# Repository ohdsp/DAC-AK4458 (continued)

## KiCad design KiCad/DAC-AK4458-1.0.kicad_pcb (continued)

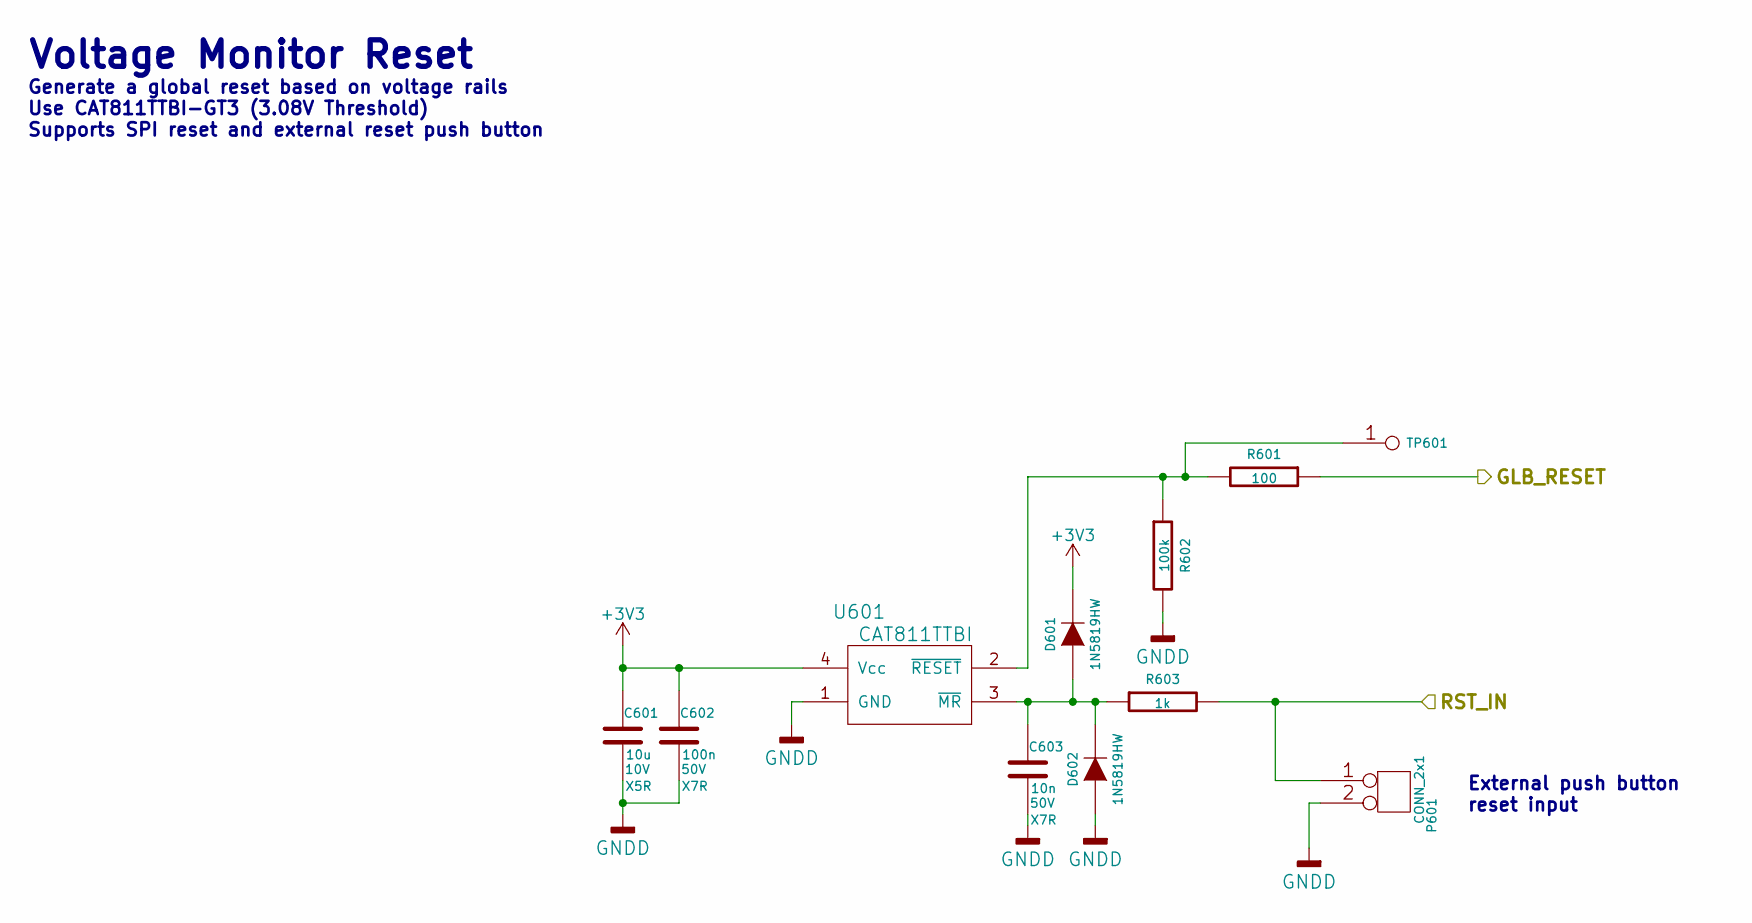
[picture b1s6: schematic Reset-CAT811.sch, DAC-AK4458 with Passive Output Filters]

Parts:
C601: 10u; SMD-0805; Voltage 10V; Tolerance 20%
C602: 100n; SMD-0805; Voltage 50V; Tolerance 10%
C603: 10n; SMD-0805; Voltage 50V; Tolerance 10%
D601, D602: 1N5819HW; DIODE-SOD-123
P601: CONN_2x1; CONN_SIL_2_1MM
R601: 100; SMD-0805; Tolerance 1%
R602: 100k; SMD-0805; Tolerance 1%
R603: 1k; SMD-0805; Tolerance 1%
TP601: PIN; TP-2mm
U601: CAT811TTBI; IC-SOT143

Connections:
+3V3: C601.1, C602.1, D601.2 (K), U601.4 (Vcc); also elsewhere on the board
/GLB_RST: R601.1; also elsewhere on the board
/Reset-CAT811/RST_IN: P601.1, R603.2; also elsewhere on the board
GNDA: C601.2, C602.2, C603.2, D602.1 (A), P601.2, R602.2, U601.1 (GND); also elsewhere on the board
unnamed: C603.1, D601.1 (A), D602.2 (K), R603.1, U601.3 (~MR)
unnamed: R601.2, R602.1, TP601.1, U601.2 (~RESET)

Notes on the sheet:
Generate a global reset based on voltage rails Use CAT811TTBI−GT3 (3.08V Threshold) Supports SPI reset and external reset push button
Voltage Monitor Reset
External push button reset input

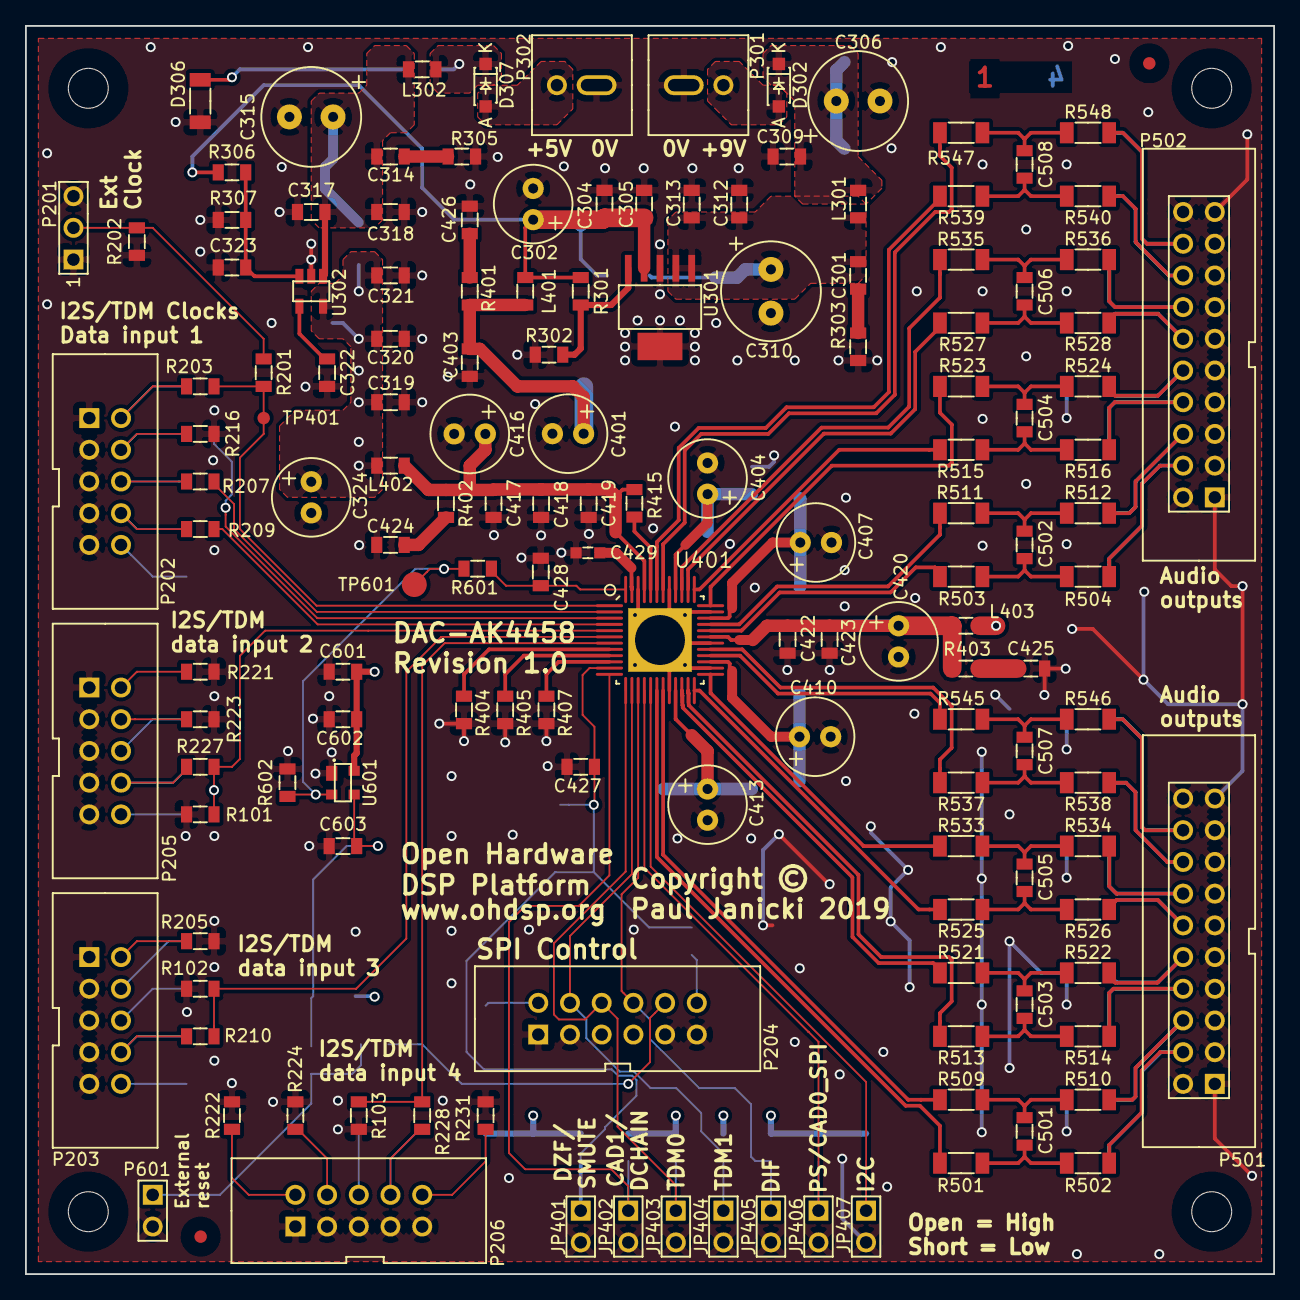
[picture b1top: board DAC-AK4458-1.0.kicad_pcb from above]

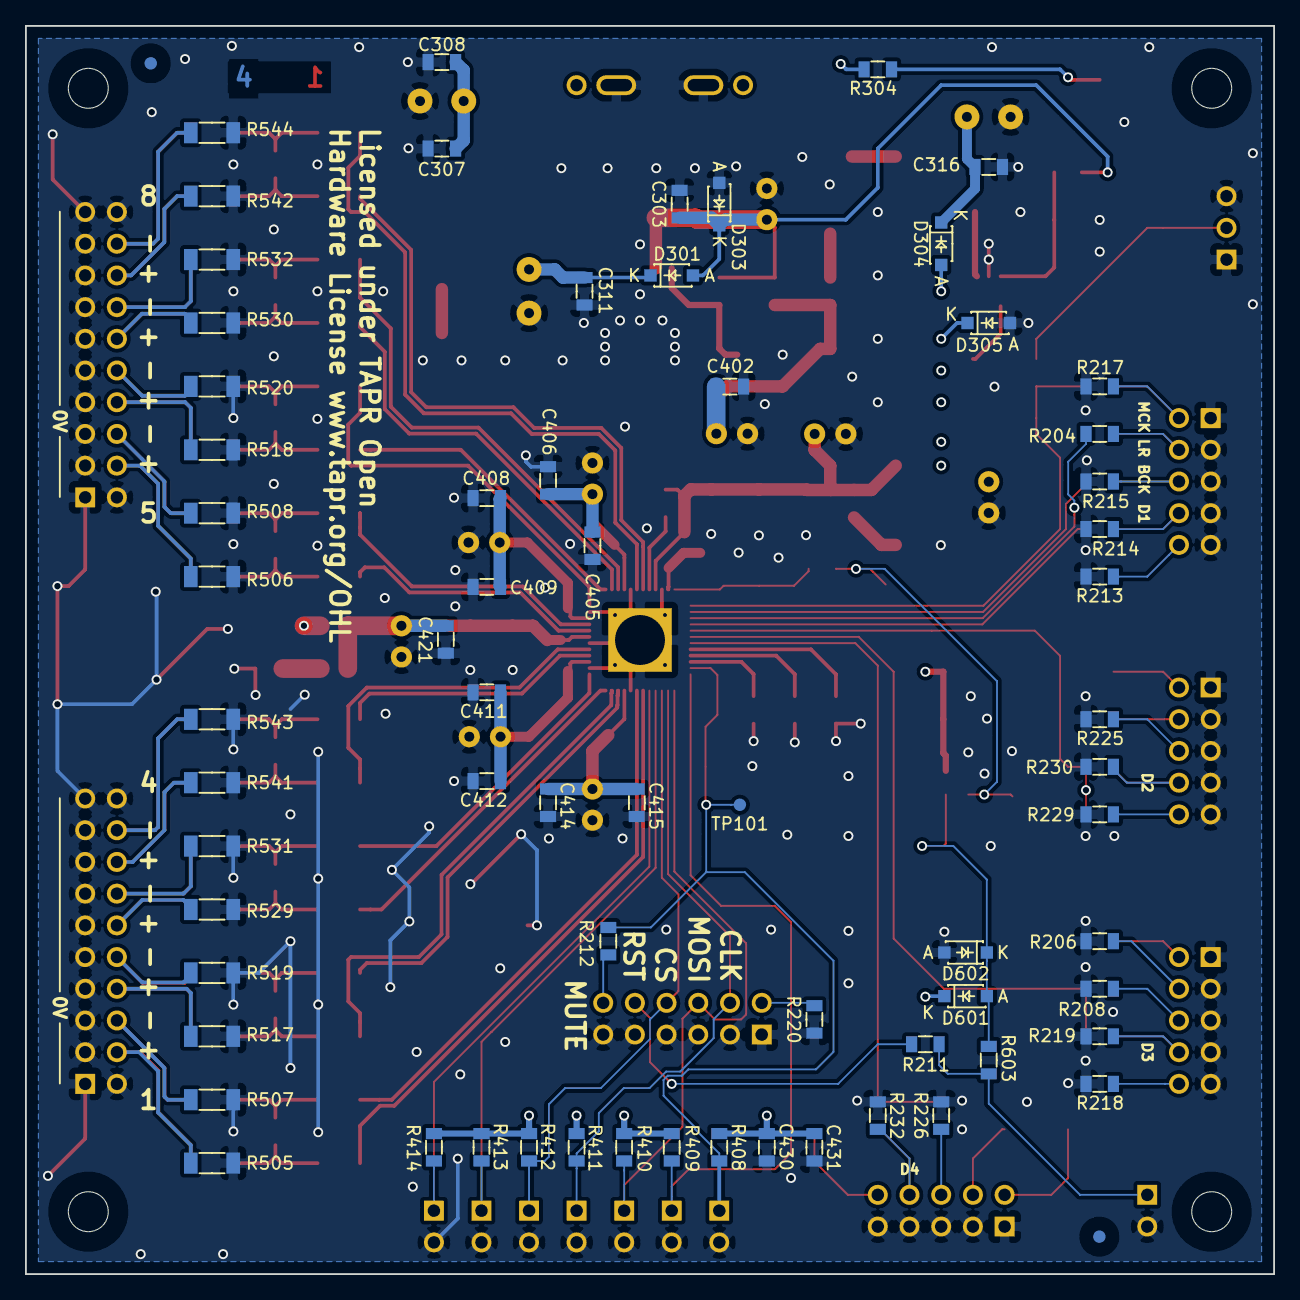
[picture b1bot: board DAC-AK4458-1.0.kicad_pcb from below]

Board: 4 copper layers, 100.0 x 100.0 mm, 220 parts (68 on the bottom side), 116 nets.

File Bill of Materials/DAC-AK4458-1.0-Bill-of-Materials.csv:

Reference; Quantity; Footprint; Value; Description; Power; Size; Tolerance; Voltage; Type; Current; 
C301 C314 C424 C425 C426 ;5;SMD-0805;100p;'Ceramic capacitor;';'0805;'5%;'50V;'C0G;';
C302 C324 C401 C416 C420 ;5;CAP-TH-D6.3mmP2.5mm;220u;'Aluminium electrolytic low impedance capacitor - eg Panasonic FC or FR parts;';'2.5mm Pitch, 6.3mm Diameter;';'10V;';';
C306 C310 C315 ;3;CAP-TH-D8mmP3.5mm;220u;'Aluminium electrolytic low impedance capacitor - eg Panasonic FC or FR parts;';'3.5mm Pitch, 8mm Diameter;';'25V;';';
C307 C311 C316 ;3;SMD-0805;22u;'Ceramic capacitor;';'0805;'20%;'25V;'X5R;';
C304 C308 C312 C317 C320 C323 C403 C405 C408 C411 C414 C418 C422 C428 C430 C602 ;16;SMD-0805;100n;'Ceramic capacitor;';'0805;'10%;'50V;'X7R;';
C305 C309 C313 C318 C321 C406 C409 C412 C415 C419 C423 C427 C603 ;13;SMD-0805;10n;'Ceramic capacitor;';'0805;'10%;'50V;'X7R;';
C303 C319 C402 C417 C421 ;5;SMD-0805;22u;'Ceramic capacitor;';'0805;'20%;'10V;'X5R;';
C322 ;1;SMD-0805;N/F;'Ceramic capacitor - NOT FITTED;';'0805;'10%;'50V;'X7R;';
C404 C407 C410 C413 ;4;CAP-TH-D6.3mmP2.5mm;47u;'Aluminium electrolytic low impedance capacitor - eg Panasonic FC or FR parts;';'2.5mm Pitch, 6.3mm Diameter;';'10V;';';
C429 ;1;SMD-0603;1u;'Ceramic capacitor;';'0603;'10%;'10V;'X7R;';
C431 C601 ;2;SMD-0805;10u;'Ceramic capacitor;';'0805;'20%;'10V;'X5R;';
C501 C502 C503 C504 C505 C506 C507 C508 ;8;SMD-0805;2n7;'Ceramic capacitor;';'0805;'5%;'50V;'C0G;';
D301 D302 D303 D304 D305 D307 D601 D602 ;8;DIODE-SOD-123;1N5819HW;'1A 40V Schottky Rectifier - SOD-123;';';';';';';
D306 ;1;SMD-1206;Green LED 1206;'Green LED - SMD - Vf 1.8V to 2.2V;';'1206;';';';';
FID301 FID302 FID303 FID304 ;4;FID-1MM-3MM;MNT_HOLE;'Fiducial;';';';';';';
JP401 JP402 JP403 JP404 JP405 JP406 JP407 P601 ;8;CONN_SIL_2_1MM;CONN_2x1;'1x2 2.54mm pitch pin header;';';';';';';
L301 L302 L401 L402 L403 ;5;SMD-0805;600R@100MHz;'Ferrite bead, current rating 0.3A or higher, 600R@100MHz;';'0805;';';';'=>0.3A;
MNT301 MNT302 MNT303 MNT304 ;4;MNT_HOLE_3.2mm;MNT_HOLE;
P201 ;1;CONN_SIL_3_1MM;CONN_3x1;'1x3 2.54mm pitch pin header;';';';';';';
P202 P203 P205 P206 ;4;CONN_DIL_2X5_BOX_1MM;CONN_02X05;'2x5 2.54mm pitch box header;';';';';';';
P204 ;1;CONN_DIL_2X6_BOX_1MM;CONN_02X06;'2x6 2.54mm pitch box header;';';';';';';
P301 P302 ;2;CONN-2WAY-2.54mm-3.81mm-SPACING;CONN_2x1;'2 way screw terminal, 2.54mm to 3.81mm pitch;';';';';';';
P501 P502 ;2;CONN_DIL_2X10_BOX_1MM;CONN_02X10;'2x10 2.54mm pitch box header;';';';';';';
R101 R102 R103 R213 R218 R220 R229 R231 R304 R603 ;10;SMD-0805;1k;'Thick or thin film resistor;'100mW;'0805;'1%;';';';
R201 R202 R214 R215 R216 R217 R219 R230 R232 ;9;SMD-0805;N/F;'Thick or thin film resistor;'100mW;'0805;'1%;';';';
R203 R204 R207 R209 R210 R211 R212 R227 R228 R404 R405 R407 R415 ;13;SMD-0805;0;'Thick or thin film resistor;'100mW;'0805;'1%;';';';
R205 R206 R208 R221 R222 R223 R224 R225 R226 R408 R409 R410 R411 R412 R413 R414 ;16;SMD-0805;10k;'Thick or thin film resistor;'100mW;'0805;'1%;';';';
R301 ;1;SMD-0805;6k8;'Thick or thin film resistor;'100mW;'0805;'1%;';';';
R302 ;1;SMD-0805;2k2;'Thick or thin film resistor;'100mW;'0805;'1%;';';';
R303 R305 R401 R402 R403 ;5;SMD-0805;47;'Thick or thin film resistor;'100mW;'0805;'1%;';';';
R306 ;1;SMD-0805;10K;'Thick or thin film resistor;'100mW;'0805;'1%;';';';
R307 ;1;SMD-0805;220K;'Thick or thin film resistor;'100mW;'0805;'1%;';';';
R501 R503 R509 R511 R513 R515 R521 R523 R525 R527 R533 R535 R537 R539 R545 R547 ;16;SMD-1206;240;'MELF0204 1% =>250mW or 1206 1% =>250mW;'250mW;'1206;'1%;';';';
R502 R504 R510 R512 R514 R516 R522 R524 R526 R528 R534 R536 R538 R540 R546 R548 ;16;SMD-1206;100;'MELF0204 1% =>250mW or 1206 1% =>250mW;'250mW;'1206;'1%;';';';
R505 R506 R507 R508 R517 R518 R519 R520 R529 R530 R531 R532 R541 R542 R543 R544 ;16;SMD-1206;100k;'MELF0204 1% =>250mW or 1206 1% =>250mW;'250mW;'1206;'1%;';';';
R601 ;1;SMD-0805;100;'Thick or thin film resistor;'100mW;'0805;'1%;';';';
R602 ;1;SMD-0805;100k;'Thick or thin film resistor;'100mW;'0805;'1%;';';';
TP101 ;1;TP-1mm;Test point;'1mm test point;';';';';';';
TP401 ;1;TP-1mm;Test point;'Test point;';';';';';';
TP601 ;1;TP-2mm;PIN;
U301 ;1;IC-SOT223-6;TPS7A4501DCQ;'TI TPS7A4501DCQ Regulator;';';';';';';
U302 ;1;IC-SOT23-5;TLV70033DDC;'TLV700 200-mA, Low-IQ, Low-Dropout Regulator;';';';';';';
U401 ;1;IC_QFN_48_5.1mmpad_HF_HS;AK4458VN;'AK4458 8ch Premium DAC;';';';';';';
U601 ;1;IC-SOT143;CAT811TTBI;'CAT811/ADM811 - 4-Pin Microprocessor Power Supply Supervisor with Manual Reset - Active Low;';';';';';';

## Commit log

2019-04-03 DAC-AK4458-1.0
    DAC-AK4458-1.0
2019-04-03 DAC-AK4458-1.0
    DAC-AK4458-1.0
    Fix gerber front mask error
